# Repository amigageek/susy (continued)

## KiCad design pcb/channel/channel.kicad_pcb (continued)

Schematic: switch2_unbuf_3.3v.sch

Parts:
Q4, Q5, Q6: MBT3946DW1T1; SOT-363_SC-70-6
R51, R52, R53, R54, R55, R56, R57, R58: 100k; R_0603_1608Metric_Pad1.05x0.95mm_HandSolder

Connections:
/Switch4 (3.3V)/OUT: Q5.3 (C2), Q5.6 (C1), Q6.3 (C2), Q6.6 (C1); also elsewhere on the board
/Switch4 (3.3V)/Switch4 (3.3V) 12-34/SIGNAL1: Q6.1 (E1), Q6.4 (E2); also elsewhere on the board
/Switch4 (3.3V)/Switch4 (3.3V) 12-34/SIGNAL2: Q5.1 (E1), Q5.4 (E2); also elsewhere on the board
GND: Q4.1 (E1), R53.2; also elsewhere on the board
unnamed: Q4.2 (B1), R52.1
unnamed: Q4.3 (C2), R53.1, R55.2
unnamed: Q4.5 (B2), R51.1
unnamed: Q4.6 (C1), R54.2, R56.2
unnamed: Q5.2 (B1), R57.1
unnamed: Q5.5 (B2), R55.1
unnamed: Q6.2 (B1), R56.1
unnamed: Q6.5 (B2), R58.1
OSELB: R51.2, R52.2, R57.2, R58.2; also elsewhere on the board
VCC: Q4.4 (E2), R54.1; also elsewhere on the board

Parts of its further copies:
Q7, Q8, Q9, Q10, Q11, Q12: MBT3946DW1T1; SOT-363_SC-70-6
R59, R60, R61, R62, R63, R64, R65, R66, R67, R68, R69, R70, R71, R72, R73, R74: 100k; R_0603_1608Metric_Pad1.05x0.95mm_HandSolder

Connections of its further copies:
/Switch4 (3.3V)/SIGNAL1: Q9.1 (E1), Q9.4 (E2); also elsewhere on the board
/Switch4 (3.3V)/SIGNAL2: Q8.1 (E1), Q8.4 (E2); also elsewhere on the board
/Switch4 (3.3V)/SIGNAL3: Q12.1 (E1), Q12.4 (E2); also elsewhere on the board
/Switch4 (3.3V)/SIGNAL4: Q11.1 (E1), Q11.4 (E2); also elsewhere on the board
/Switch4 (3.3V)/Switch4 (3.3V) 1-2/OUT1: Q12.3 (C2), Q12.6 (C1); also elsewhere on the board
/Switch4 (3.3V)/Switch4 (3.3V) 1-2/OUT2: Q11.3 (C2), Q11.6 (C1); also elsewhere on the board
/Switch4 (3.3V)/Switch4 (3.3V) 3-4/OUT1: Q9.3 (C2), Q9.6 (C1); also elsewhere on the board
/Switch4 (3.3V)/Switch4 (3.3V) 3-4/OUT2: Q8.3 (C2), Q8.6 (C1); also elsewhere on the board
GND: Q7.1 (E1), Q10.1 (E1), R61.2, R69.2; also elsewhere on the board
unnamed: Q7.2 (B1), R60.1
unnamed: Q7.3 (C2), R61.1, R63.2
unnamed: Q7.5 (B2), R59.1
unnamed: Q7.6 (C1), R62.2, R64.2
unnamed: Q8.2 (B1), R65.1
unnamed: Q8.5 (B2), R63.1
unnamed: Q9.2 (B1), R64.1
unnamed: Q9.5 (B2), R66.1
unnamed: Q10.2 (B1), R68.1
unnamed: Q10.3 (C2), R69.1, R71.2
unnamed: Q10.5 (B2), R67.1
unnamed: Q10.6 (C1), R70.2, R72.2
unnamed: Q11.2 (B1), R73.1
unnamed: Q11.5 (B2), R71.1
unnamed: Q12.2 (B1), R72.1
unnamed: Q12.5 (B2), R74.1
OSELA: R59.2, R60.2, R65.2, R66.2, R67.2, R68.2, R73.2, R74.2; also elsewhere on the board
VCC: Q7.4 (E2), Q10.4 (E2), R62.1, R70.1; also elsewhere on the board

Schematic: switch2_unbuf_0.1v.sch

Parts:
IC14: DMC2700UDM-7; SOT95P285X140-6N; Manufacturer_Part_Number DMC2700UDM-7; Mouser Part Number 621-DMC2700UDM-7
R125: 4.7k; R_0603_1608Metric_Pad1.05x0.95mm_HandSolder

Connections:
/Switch4 (0.1V)/Switch4 (0.1V) 1-2/OUT: IC14.4 (D2), IC14.6 (D1); also elsewhere on the board
/Switch4 (0.1V)/Switch4 (0.1V) 1-2/SIGNAL1: IC14.2 (S2); also elsewhere on the board
/Switch4 (0.1V)/Switch4 (0.1V) 1-2/SIGNAL2: IC14.5 (S1); also elsewhere on the board
FSELA: R125.2; also elsewhere on the board
unnamed: IC14.1 (G1), IC14.3 (G2), R125.1

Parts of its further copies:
IC10, IC15, IC16: DMC2700UDM-7; SOT95P285X140-6N; Manufacturer_Part_Number DMC2700UDM-7; Mouser Part Number 621-DMC2700UDM-7
R77, R126, R127: 4.7k; R_0603_1608Metric_Pad1.05x0.95mm_HandSolder

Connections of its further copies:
/Switch2 (0.1V)/OP+: IC10.4 (D2), IC10.6 (D1); also elsewhere on the board
/Switch2 (0.1V)/Switch2 (0.1V) 1-2/SIGNAL1: IC10.2 (S2); also elsewhere on the board
/Switch2 (0.1V)/Switch2 (0.1V) 1-2/SIGNAL2: IC10.5 (S1); also elsewhere on the board
/Switch4 (0.1V)/OP+: IC16.4 (D2), IC16.6 (D1); also elsewhere on the board
/Switch4 (0.1V)/Switch4 (0.1V) 1-2/OUT: IC16.2 (S2); also elsewhere on the board
/Switch4 (0.1V)/Switch4 (0.1V) 3-4/OUT: IC15.4 (D2), IC15.6 (D1), IC16.5 (S1)
/Switch4 (0.1V)/Switch4 (0.1V) 3-4/SIGNAL1: IC15.2 (S2); also elsewhere on the board
/Switch4 (0.1V)/Switch4 (0.1V) 3-4/SIGNAL2: IC15.5 (S1); also elsewhere on the board
FSELA: R126.2; also elsewhere on the board
FSELB: R127.2; also elsewhere on the board
unnamed: IC10.1 (G1), IC10.3 (G2), R77.1
unnamed: IC15.1 (G1), IC15.3 (G2), R126.1
unnamed: IC16.1 (G1), IC16.3 (G2), R127.1
RMSEL: R77.2; also elsewhere on the board

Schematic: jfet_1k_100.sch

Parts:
Q15: 2SK3557-7-TB-E; SOT95P250X135-3N; Manufacturer_Part_Number 2SK3557-7-TB-E; Mouser Part Number 863-2SK3557-7-TB-E
R103, R104, R105, R106: 1; R_0603_1608Metric_Pad1.05x0.95mm_HandSolder
R107, R108: 100k; R_0603_1608Metric_Pad1.05x0.95mm_HandSolder

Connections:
/Filter/JFET 1K-100 (1)/DRAIN: Q15.2 (DRAIN); also elsewhere on the board
/Filter/JFET 1K-100 (1)/OP1+: R103.1, R104.2; also elsewhere on the board
/Filter/JFET 1K-100 (1)/OP1-: R105.2, R106.1; also elsewhere on the board
/Filter/JFET 1K-100 (1)/OP1O: R106.2, R107.1; also elsewhere on the board
/Filter/JFET 1K-100 (1)/OP2-: R108.1; also elsewhere on the board
/Filter/RESON: R103.2; also elsewhere on the board
unnamed: Q15.3 (GATE), R107.2, R108.2
VCC: R105.1; also elsewhere on the board
VGND: Q15.1 (SOURCE); also elsewhere on the board
VHALF: R104.1; also elsewhere on the board

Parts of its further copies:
Q16, Q17: 2SK3557-7-TB-E; SOT95P250X135-3N; Manufacturer_Part_Number 2SK3557-7-TB-E; Mouser Part Number 863-2SK3557-7-TB-E
R109, R110, R111, R112, R115, R116, R117, R118: 1; R_0603_1608Metric_Pad1.05x0.95mm_HandSolder
R113, R114, R119, R120: 100k; R_0603_1608Metric_Pad1.05x0.95mm_HandSolder

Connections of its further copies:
/Filter/BAND: Q16.2 (DRAIN); also elsewhere on the board
/Filter/CUTOFF: R109.2, R115.2; also elsewhere on the board
/Filter/HIGH: Q17.2 (DRAIN); also elsewhere on the board
/Filter/JFET 1K-100 (2)/OP2-: R120.1; also elsewhere on the board
/Filter/JFET 1K-100 (2)/SOURCE: Q17.1 (SOURCE); also elsewhere on the board
/Filter/JFET 1K-100 (3)/OP1+: R109.1, R110.2; also elsewhere on the board
/Filter/JFET 1K-100 (3)/OP1-: R111.2, R112.1; also elsewhere on the board
/Filter/JFET 1K-100 (3)/OP1O: R112.2, R113.1; also elsewhere on the board
/Filter/JFET 1K-100 (3)/OP2-: R114.1; also elsewhere on the board
/Filter/JFET 1K-100 (3)/SOURCE: Q16.1 (SOURCE); also elsewhere on the board
/Filter/OP+: R115.1, R116.2; also elsewhere on the board
/Filter/OP-: R117.2, R118.1; also elsewhere on the board
/Filter/OPO: R118.2, R119.1; also elsewhere on the board
unnamed: Q16.3 (GATE), R113.2, R114.2
unnamed: Q17.3 (GATE), R119.2, R120.2
VCC: R111.1, R117.1; also elsewhere on the board
VHALF: R110.1, R116.1; also elsewhere on the board

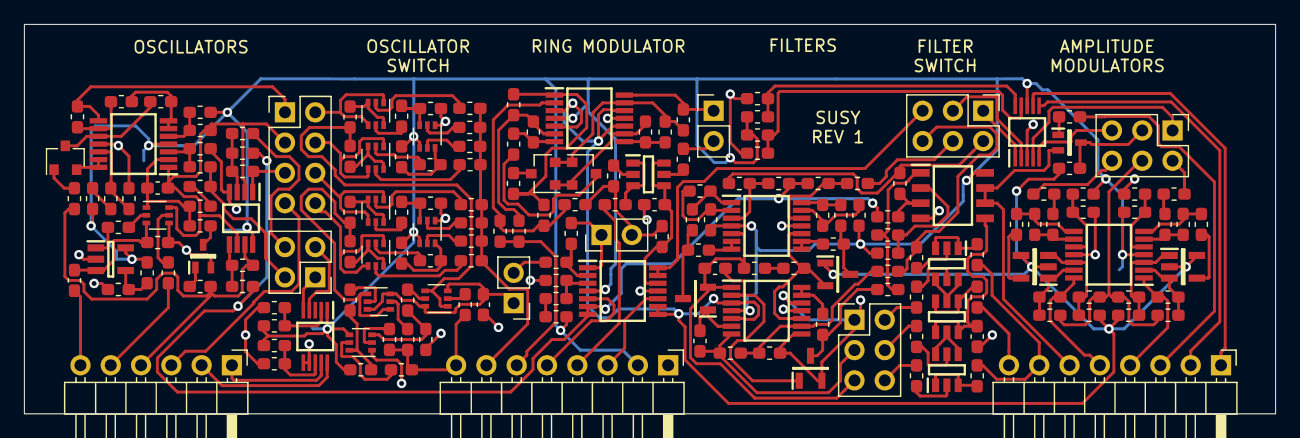
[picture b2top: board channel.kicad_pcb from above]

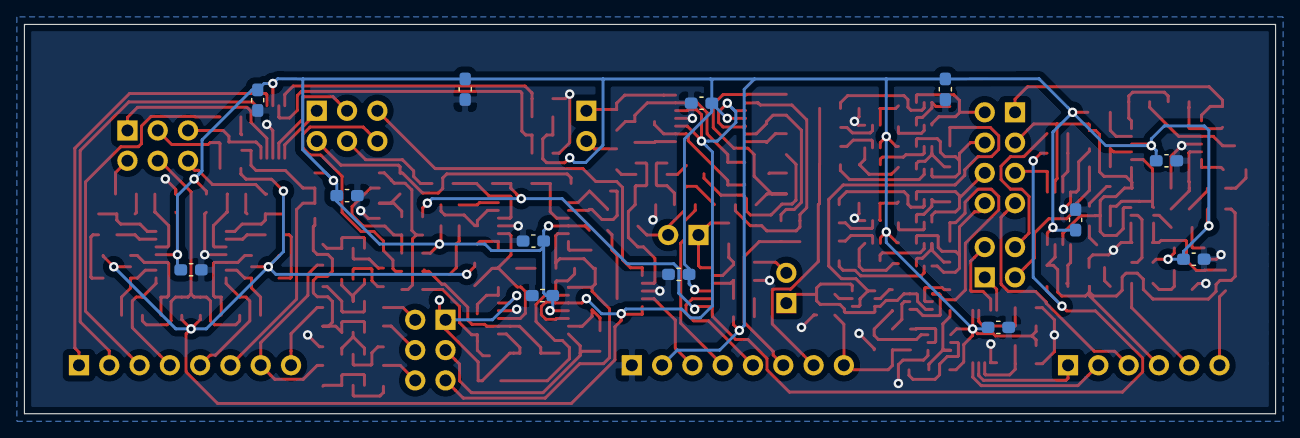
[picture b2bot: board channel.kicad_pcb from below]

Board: 2 copper layers, 104.9 x 32.6 mm, 199 parts (13 on the bottom side), 174 nets.

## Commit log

2020-12-20 Add LTspice analog simulations
2021-03-16 Add channel PCB revision 1
2021-03-17 Replace component cache with symbol/footprint source
2021-03-17 Match simulation components to PCB, tweak top-level simulations
2021-05-17 Fix attenuator JFET calibration math
2021-05-17 Reduce JFET base resistor from 1Meg to 100K
    Precaution against too much voltage drop to base
2021-05-17 Set final resistor values for oscillator
2021-05-17 Increase ring modulator gain for 100mVpp output
2021-05-17 Substitute available resistor values
2021-05-17 Rename/renumbering (I think)
2021-06-12 Add channel-cache.lib
2022-05-02 Add interface PCB files
